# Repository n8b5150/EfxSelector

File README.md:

# EfxSelector
Open source, programmable guitar effects selector.

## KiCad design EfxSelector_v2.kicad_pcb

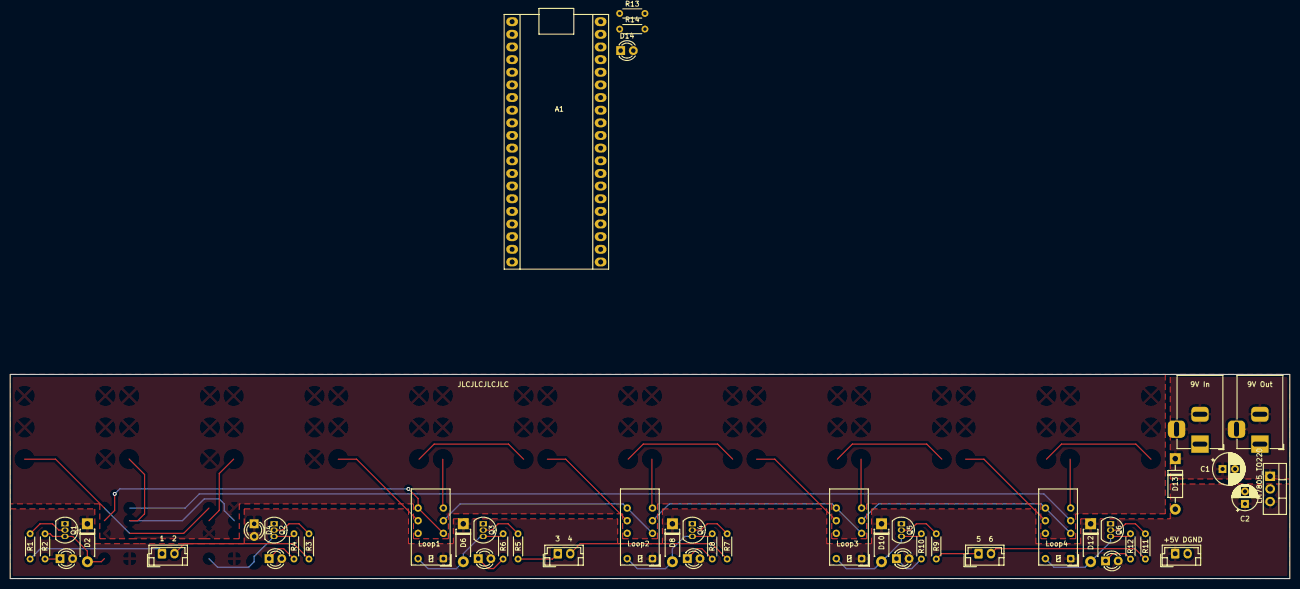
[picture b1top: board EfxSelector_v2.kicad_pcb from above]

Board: 2 copper layers, 257.0 x 41.0 mm, 48 parts (0 on the bottom side), 31 nets.

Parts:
A1: Raspberry_Pi_Pico_THT; raspberry_pi_pico_THT
C1: C_Polarized_US; CP_Radial_D6.3mm_P2.50mm
C2: C_Polarized_US; CP_Radial_D5.0mm_P2.50mm
D1, D3, D4, D5, D7, D9, D11, D14: IR204A; LED_D3.0mm
D2, D6, D8, D10, D12: 1N4001; D_DO-41_SOD81_P7.62mm_Horizontal
D13: 1N4001; D_DO-41_SOD81_P10.16mm_Horizontal
J4, J12, J34, J56: Conn_01x02; JST_EH_B2B-EH-A_1x02_P2.50mm_Vertical
JDC1, JDC2: Barrel_Jack_Switch; BarrelJack_Horizontal
Loop1, Loop2, Loop3, Loop4: EC2-4.5NU; Relay_DPDT_Kemet_EC2
Q1, Q2, Q3, Q4, Q5, Q6: 2N3904; TO-92_Inline
R1, R2, R3, R4, R5, R6, R7, R8, R9, R10, R11, R12, R13, R14: R_Small_US; R_Axial_DIN0204_L3.6mm_D1.6mm_P5.08mm_Horizontal
U1: LM7805_TO220; TO-220-3_Vertical

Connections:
+5V: C2.1, D1.2 (A), D2.1 (K), D5.2 (A), D6.1 (K), D7.2 (A), D8.1 (K), D9.2 (A), D10.1 (K), D11.2 (A), D12.1 (K), J4.1, Loop1.1, Loop2.1, Loop3.1, Loop4.1, U1.3 (VO)
+9V: C1.1, D13.1 (K), JDC1.2, JDC1.3, JDC2.2, JDC2.3, U1.1 (VI)
GND: C1.2, C2.2, D13.2 (A), J4.2, JDC1.1, JDC2.1, Q1.1 (E), Q2.1 (E), Q3.1 (E), Q4.1 (E), Q5.1 (E), Q6.1 (E), U1.2 (GND)
J12-1: J12.1, R1.2
J12-3: J34.1, R5.2
J12-4: J34.2, R7.2
J12-5: J56.1, R9.2
J12-6: J56.2, R3.2, R11.2
L-In: Loop1.3, Loop1.8
unnamed: D1.1 (K), R2.2
unnamed: D2.2 (A), Q1.3 (C), R2.1
unnamed: D3.1 (K), R4.2
unnamed: D4.1 (K), R13.2
unnamed: D5.1 (K), R6.2
unnamed: D6.2 (A), Loop1.12, Q3.3 (C), R6.1
unnamed: D7.1 (K), R8.2
unnamed: D8.2 (A), Loop2.12, Q4.3 (C), R8.1
unnamed: D9.1 (K), R10.2
unnamed: D10.2 (A), Loop3.12, Q5.3 (C), R10.1
unnamed: D11.1 (K), R12.2
unnamed: D12.2 (A), Loop4.12, Q6.3 (C), R12.1
unnamed: D14.1 (K), R14.2
unnamed: Loop1.4, Loop2.3, Loop2.8
unnamed: Loop2.4, Loop3.3, Loop3.8
unnamed: Loop3.4, Loop4.3, Loop4.8
unnamed: Q1.2 (B), R1.1
unnamed: Q2.2 (B), R3.1
unnamed: Q3.2 (B), R5.1
unnamed: Q4.2 (B), R7.1
unnamed: Q5.2 (B), R9.1
unnamed: Q6.2 (B), R11.1

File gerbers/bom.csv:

Designator,Footprint,Quantity,Value,LCSC Part #
D13,D_DO-41_SOD81_P10.16mm_Horizontal,1,1N4001,
D9,LED_D3.0mm,1,IR204A,
R1,R_Axial_DIN0204_L3.6mm_D1.6mm_P5.08mm_Horizontal,1,R_Small_US,
JDC1,BarrelJack_Horizontal,1,Barrel_Jack_Switch,
L2-In,Jack_6.35mm_Neutrik_NMJ6HCD2_Horizontal,1,AudioJack3_SwitchSTR,
In,Jack_6.35mm_Neutrik_NMJ6HCD2_Horizontal,1,AudioJack3_SwitchSTR,
D4,D_DO-41_SOD81_P7.62mm_Horizontal,1,1N4001,
Q3,TO-92_Inline,1,2N3904,
Bypass,Relay_DPDT_Kemet_EC2,1,EC2-4.5NU,
Q4,TO-92_Inline,1,2N3904,
J4,JST_EH_B2B-EH-A_1x02_P2.50mm_Vertical,1,Conn_01x02,
R3,R_Axial_DIN0204_L3.6mm_D1.6mm_P5.08mm_Horizontal,1,R_Small_US,
R9,R_Axial_DIN0204_L3.6mm_D1.6mm_P5.08mm_Horizontal,1,R_Small_US,
Q2,TO-92_Inline,1,2N3904,
Loop3,Relay_DPDT_Kemet_EC2,1,EC2-4.5NU,
R5,R_Axial_DIN0204_L3.6mm_D1.6mm_P5.08mm_Horizontal,1,R_Small_US,
C2,CP_Radial_D5.0mm_P2.50mm,1,C_Polarized_US,
D12,D_DO-41_SOD81_P7.62mm_Horizontal,1,1N4001,
Loop1,Relay_DPDT_Kemet_EC2,1,EC2-4.5NU,
R4,R_Axial_DIN0204_L3.6mm_D1.6mm_P5.08mm_Horizontal,1,R_Small_US,
Q1,TO-92_Inline,1,2N3904,
R10,R_Axial_DIN0204_L3.6mm_D1.6mm_P5.08mm_Horizontal,1,R_Small_US,
Loop4,Relay_DPDT_Kemet_EC2,1,EC2-4.5NU,
Tuner_2,Jack_6.35mm_Neutrik_NMJ6HCD2_Horizontal,1,AudioJack3_SwitchSTR,
Tuner,Relay_DPDT_Kemet_EC2,1,EC2-4.5NU,
Q6,TO-92_Inline,1,2N3904,
L2-Out,Jack_6.35mm_Neutrik_NMJ6HCD2_Horizontal,1,AudioJack3_SwitchSTR,
L1-In,Jack_6.35mm_Neutrik_NMJ6HCD2_Horizontal,1,AudioJack3_SwitchSTR,
R8,R_Axial_DIN0204_L3.6mm_D1.6mm_P5.08mm_Horizontal,1,R_Small_US,
R11,R_Axial_DIN0204_L3.6mm_D1.6mm_P5.08mm_Horizontal,1,R_Small_US,
J56,JST_EH_B2B-EH-A_1x02_P2.50mm_Vertical,1,Conn_01x02,
L1-Out,Jack_6.35mm_Neutrik_NMJ6HCD2_Horizontal,1,AudioJack3_SwitchSTR,
D10,D_DO-41_SOD81_P7.62mm_Horizontal,1,1N4001,
L3-Out,Jack_6.35mm_Neutrik_NMJ6HCD2_Horizontal,1,AudioJack3_SwitchSTR,
D2,D_DO-41_SOD81_P7.62mm_Horizontal,1,1N4001,
L4-In,Jack_6.35mm_Neutrik_NMJ6HCD2_Horizontal,1,AudioJack3_SwitchSTR,
U1,TO-220-3_Vertical,1,LM7805,
R7,R_Axial_DIN0204_L3.6mm_D1.6mm_P5.08mm_Horizontal,1,R_Small_US,
L4-Out,Jack_6.35mm_Neutrik_NMJ6HCD2_Horizontal,1,AudioJack3_SwitchSTR,
D3,LED_D3.0mm,1,IR204A,
J34,JST_EH_B2B-EH-A_1x02_P2.50mm_Vertical,1,Conn_01x02,
JDC2,BarrelJack_Horizontal,1,Barrel_Jack_Switch,
C1,CP_Radial_D6.3mm_P2.50mm,1,C_Polarized_US,
Loop2,Relay_DPDT_Kemet_EC2,1,EC2-4.5NU,
D1,LED_D3.0mm,1,IR204A,
R2,R_Axial_DIN0204_L3.6mm_D1.6mm_P5.08mm_Horizontal,1,R_Small_US,
L3-In,Jack_6.35mm_Neutrik_NMJ6HCD2_Horizontal,1,AudioJack3_SwitchSTR,
D8,D_DO-41_SOD81_P7.62mm_Horizontal,1,1N4001,
D6,D_DO-41_SOD81_P7.62mm_Horizontal,1,1N4001,
D7,LED_D3.0mm,1,IR204A,
R6,R_Axial_DIN0204_L3.6mm_D1.6mm_P5.08mm_Horizontal,1,R_Small_US,
D11,LED_D3.0mm,1,IR204A,
Q5,TO-92_Inline,1,2N3904,
J12,JST_EH_B2B-EH-A_1x02_P2.50mm_Vertical,1,Conn_01x02,
Out,Jack_6.35mm_Neutrik_NMJ6HCD2_Horizontal,1,AudioJack3_SwitchSTR,
R12,R_Axial_DIN0204_L3.6mm_D1.6mm_P5.08mm_Horizontal,1,R_Small_US,
D5,LED_D3.0mm,1,IR204A,

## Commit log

2022-08-05 revised silk screen
2022-08-05 created footprint library
2022-08-06 removed 9v out
2022-08-06 Revert "removed 9v out"
    This reverts commit 68eda4370ce2c703412f077e884cf7a60c7e0849.
2025-02-15 add pico files
2025-02-16 corrected pin changes
2025-03-29 updates and additions
